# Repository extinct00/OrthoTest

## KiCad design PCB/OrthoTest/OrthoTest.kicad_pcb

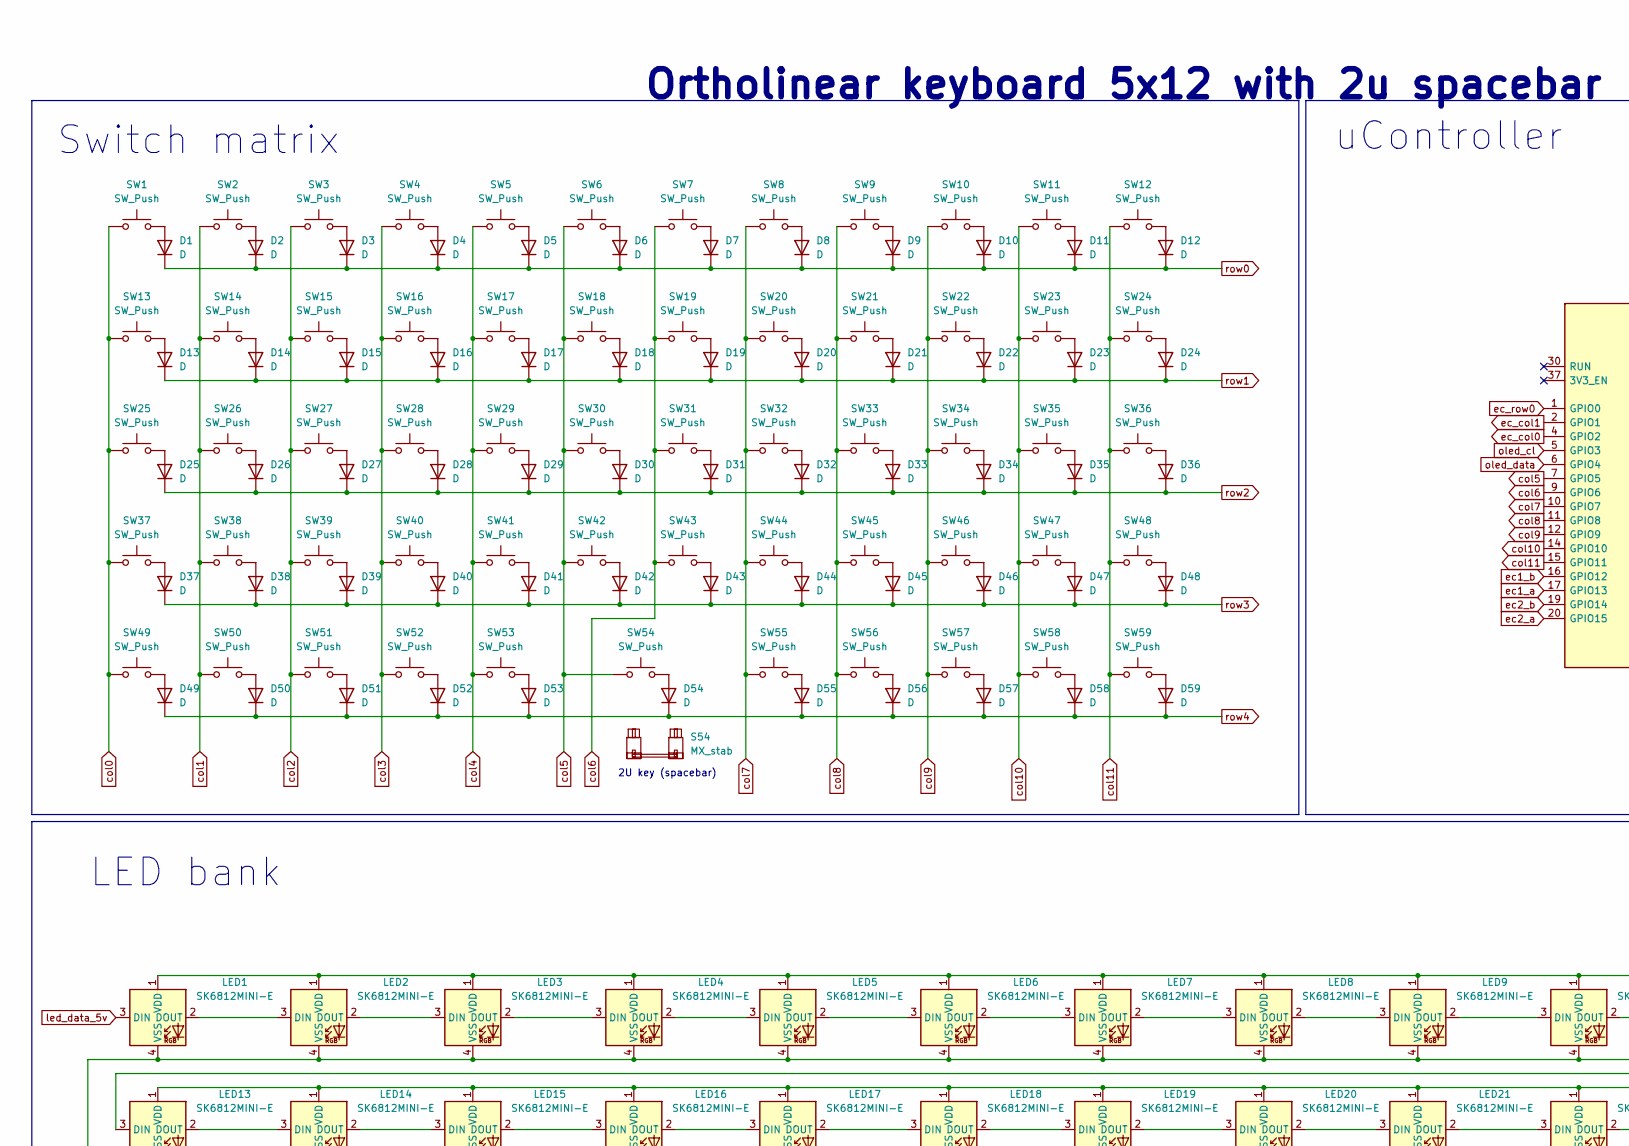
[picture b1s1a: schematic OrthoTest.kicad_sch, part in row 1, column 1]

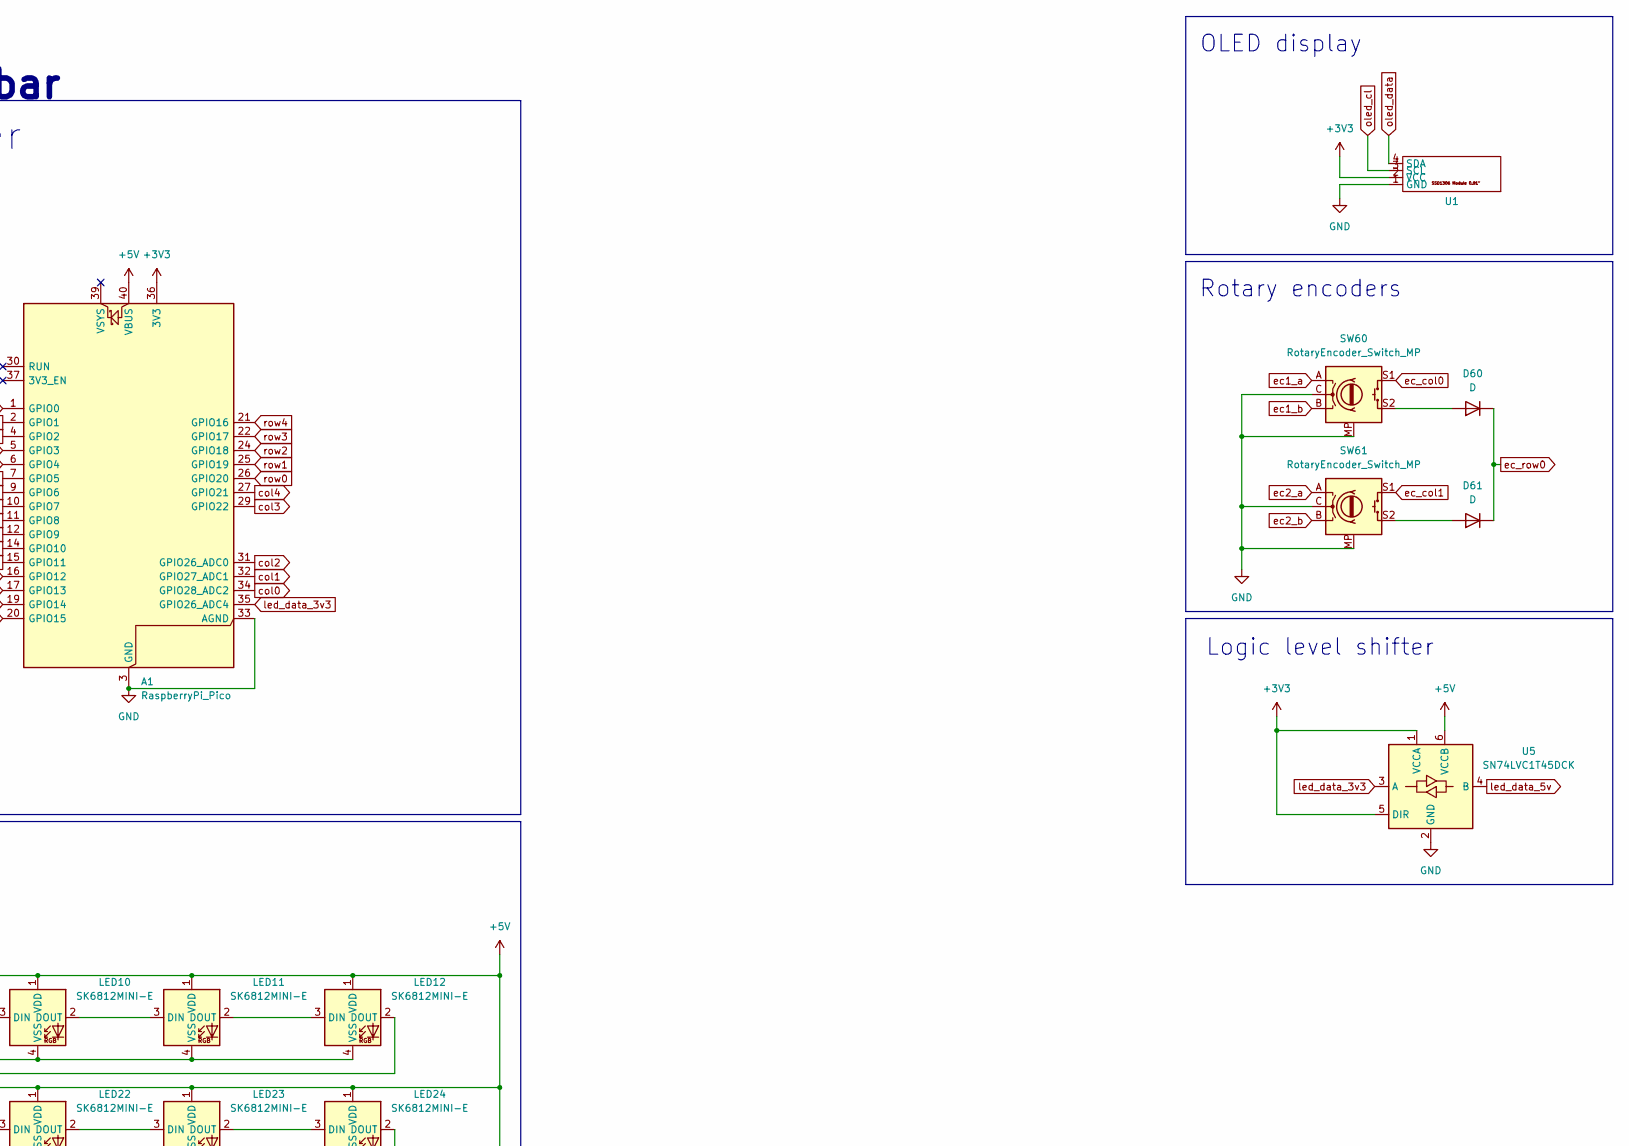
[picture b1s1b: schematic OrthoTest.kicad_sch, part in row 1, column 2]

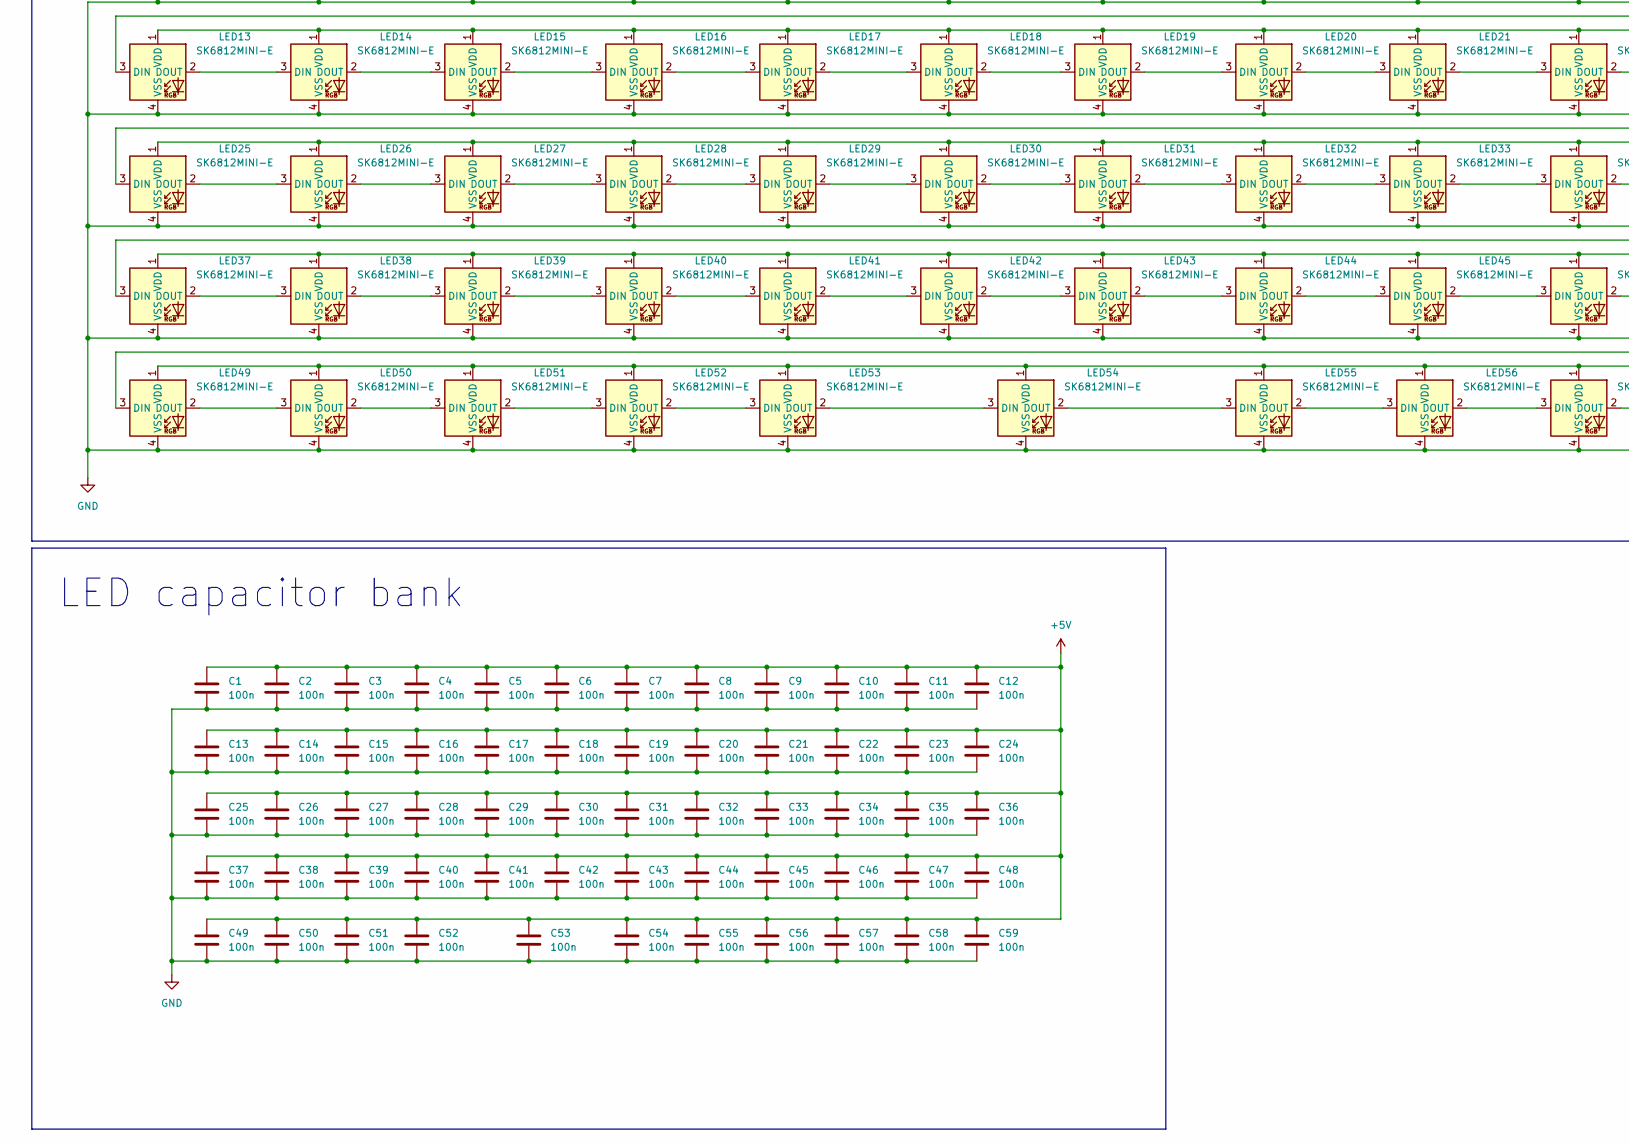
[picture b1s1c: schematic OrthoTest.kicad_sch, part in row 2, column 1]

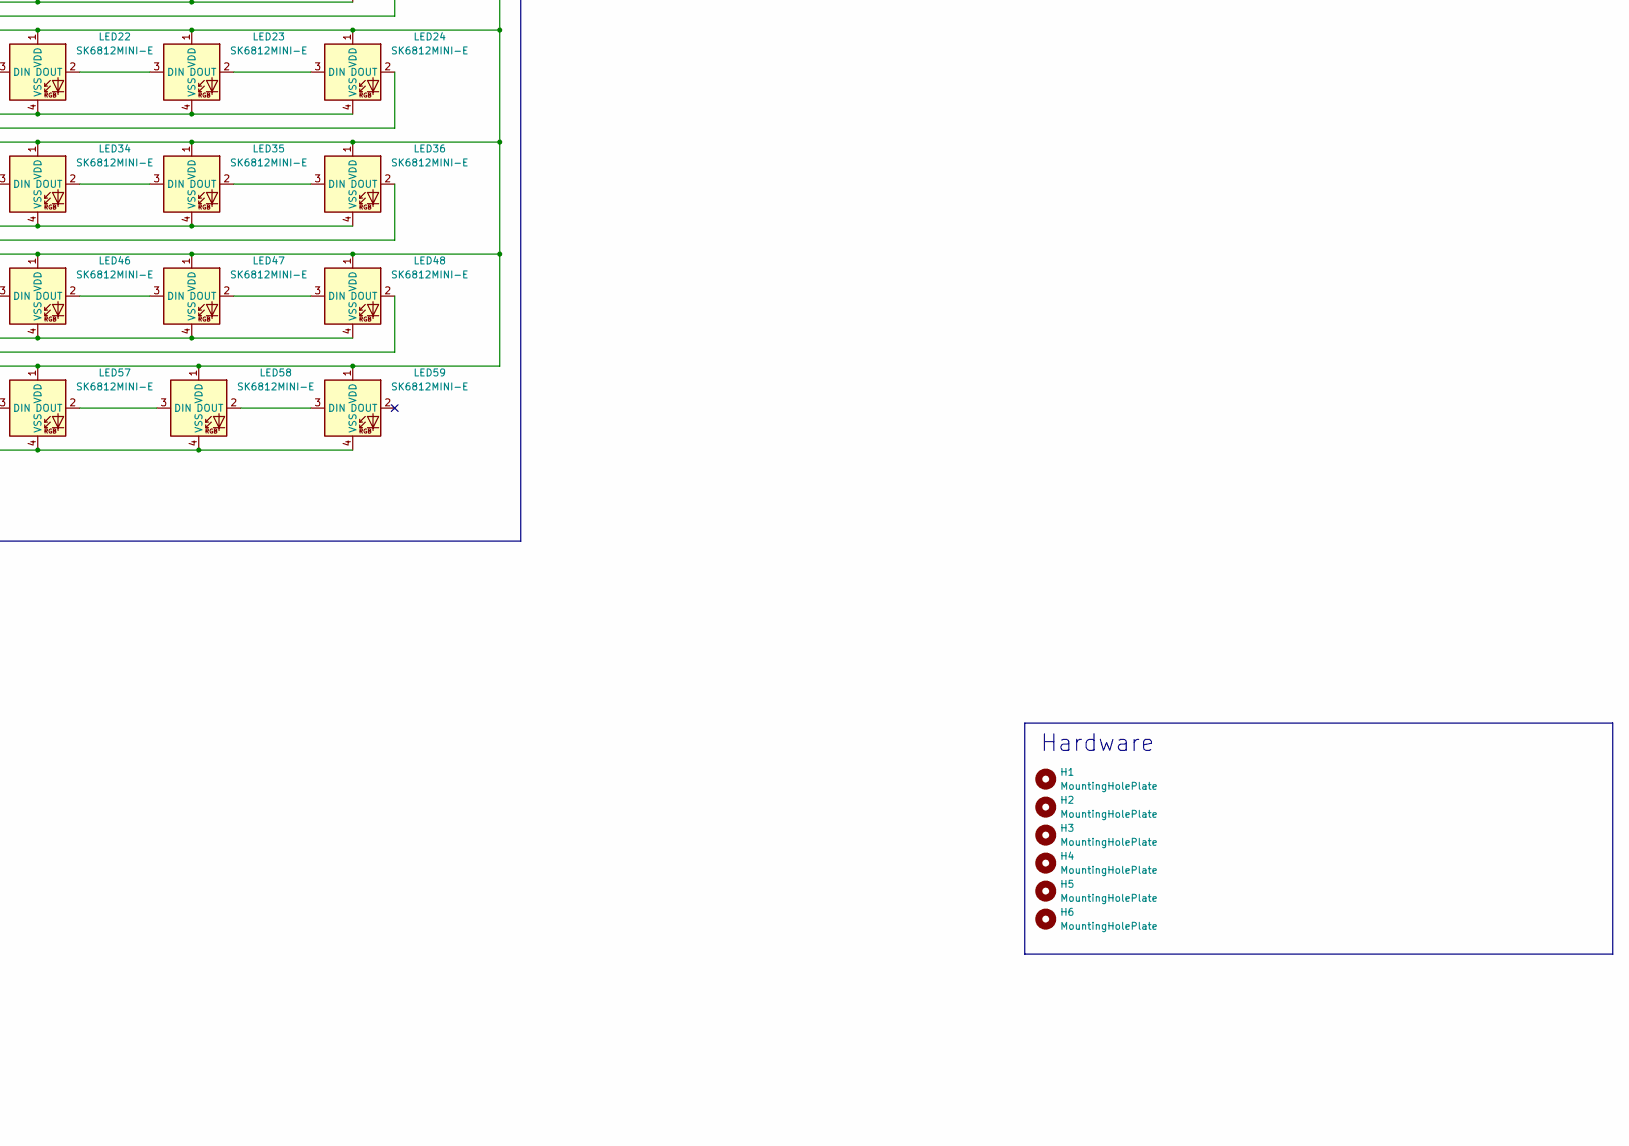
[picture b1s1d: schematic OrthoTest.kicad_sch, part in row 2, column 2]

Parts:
A1: RaspberryPi_Pico; RaspberryPi_Pico_Common_THT
C1, C2, C3, C4, C5, C6, C7, C8, C9, C10, C11, C12, C13, C14, C15, C16, C17, C18, C19, C20, C21, C22, C23, C24, C25, C26, C27, C28, C29, C30, C31, C32, C33, C34, C35, C36, C37, C38, C39, C40, C41, C42, C43, C44, C45, C46, C47, C48, C49, C50, C51, C52, C53, C54, C55, C56, C57, C58, C59: 100n; C_0603_1608Metric
D1, D2, D3, D4, D5, D6, D7, D8, D9, D10, D11, D12, D13, D14, D15, D16, D17, D18, D19, D20, D21, D22, D23, D24, D25, D26, D27, D28, D29, D30, D31, D32, D33, D34, D35, D36, D37, D38, D39, D40, D41, D42, D43, D44, D45, D46, D47, D48, D49, D50, D51, D52, D53, D54, D55, D56, D57, D58, D59, D60, D61: D; D_SOD-123_SmallArrow
H1, H2, H3, H4, H5, H6: MountingHolePlate; Spacer_3.2mm
LED1, LED2, LED3, LED4, LED5, LED6, LED7, LED8, LED9, LED10, LED11, LED12, LED13, LED14, LED15, LED16, LED17, LED18, LED19, LED20, LED21, LED22, LED23, LED24, LED25, LED26, LED27, LED28, LED29, LED30, LED31, LED32, LED33, LED34, LED35, LED36, LED37, LED38, LED39, LED40, LED41, LED42, LED43, LED44, LED45, LED46, LED47, LED48, LED49, LED50, LED51, LED52, LED53, LED54, LED55, LED56, LED57, LED58, LED59: SK6812MINI-E; LED_6028R
S54: MX_stab; STAB_MX_2u
SW1, SW2, SW3, SW4, SW5, SW6, SW7, SW8, SW9, SW10, SW11, SW12, SW13, SW14, SW15, SW16, SW17, SW18, SW19, SW20, SW21, SW22, SW23, SW24, SW25, SW26, SW27, SW28, SW29, SW30, SW31, SW32, SW33, SW34, SW35, SW36, SW37, SW38, SW39, SW40, SW41, SW42, SW43, SW44, SW45, SW46, SW47, SW48, SW49, SW50, SW51, SW52, SW53, SW54, SW55, SW56, SW57, SW58, SW59: SW_Push; SW_Redragon_LowProfile_PCB_1.00u
SW60, SW61: RotaryEncoder_Switch_MP; RotaryEncoder_Alps_EC11E-Switch_Vertical_H20mm
U1: SSD1306-0.91-OLED-4pin-128x32
U5: SN74LVC1T45DCK; SOT-363_SC-70-6

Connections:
+3V3: A1.36 (3V3), U1.2 (VCC), U5.1 (VCCA), U5.5 (DIR)
+5V: A1.40 (VBUS), C1.1, C2.1, C3.1, C4.1, C5.1, C6.1, C7.1, C8.1, C9.1, C10.1, C11.1, C12.1, C13.1, C14.1, C15.1, C16.1, C17.1, C18.1, C19.1, C20.1, C21.1, C22.1, C23.1, C24.1, C25.1, C26.1, C27.1, C28.1, C29.1, C30.1, C31.1, C32.1, C33.1, C34.1, C35.1, C36.1, C37.1, C38.1, C39.1, C40.1, C41.1, C42.1, C43.1, C44.1, C45.1, C46.1, C47.1, C48.1, C49.1, C50.1, C51.1, C52.1, C53.1, C54.1, C55.1, C56.1, C57.1, C58.1, C59.1, LED1.1 (VDD), LED2.1 (VDD), LED3.1 (VDD), LED4.1 (VDD), LED5.1 (VDD), LED6.1 (VDD), LED7.1 (VDD), LED8.1 (VDD), LED9.1 (VDD), LED10.1 (VDD), LED11.1 (VDD), LED12.1 (VDD), LED13.1 (VDD), LED14.1 (VDD), LED15.1 (VDD), LED16.1 (VDD), LED17.1 (VDD), LED18.1 (VDD), LED19.1 (VDD), LED20.1 (VDD), LED21.1 (VDD), LED22.1 (VDD), LED23.1 (VDD), LED24.1 (VDD), LED25.1 (VDD), LED26.1 (VDD), LED27.1 (VDD), LED28.1 (VDD), LED29.1 (VDD), LED30.1 (VDD), LED31.1 (VDD), LED32.1 (VDD), LED33.1 (VDD), LED34.1 (VDD), LED35.1 (VDD), LED36.1 (VDD), LED37.1 (VDD), LED38.1 (VDD), LED39.1 (VDD), LED40.1 (VDD), LED41.1 (VDD), LED42.1 (VDD), LED43.1 (VDD), LED44.1 (VDD), LED45.1 (VDD), LED46.1 (VDD), LED47.1 (VDD), LED48.1 (VDD), LED49.1 (VDD), LED50.1 (VDD), LED51.1 (VDD), LED52.1 (VDD), LED53.1 (VDD), LED54.1 (VDD), LED55.1 (VDD), LED56.1 (VDD), LED57.1 (VDD), LED58.1 (VDD), LED59.1 (VDD), U5.6 (VCCB)
GND: A1.3 (GND), A1.8 (GND), A1.13 (GND), A1.18 (GND), A1.23 (GND), A1.28 (GND), A1.33 (AGND), A1.38 (GND), C1.2, C2.2, C3.2, C4.2, C5.2, C6.2, C7.2, C8.2, C9.2, C10.2, C11.2, C12.2, C13.2, C14.2, C15.2, C16.2, C17.2, C18.2, C19.2, C20.2, C21.2, C22.2, C23.2, C24.2, C25.2, C26.2, C27.2, C28.2, C29.2, C30.2, C31.2, C32.2, C33.2, C34.2, C35.2, C36.2, C37.2, C38.2, C39.2, C40.2, C41.2, C42.2, C43.2, C44.2, C45.2, C46.2, C47.2, C48.2, C49.2, C50.2, C51.2, C52.2, C53.2, C54.2, C55.2, C56.2, C57.2, C58.2, C59.2, LED1.4 (VSS), LED2.4 (VSS), LED3.4 (VSS), LED4.4 (VSS), LED5.4 (VSS), LED6.4 (VSS), LED7.4 (VSS), LED8.4 (VSS), LED9.4 (VSS), LED10.4 (VSS), LED11.4 (VSS), LED12.4 (VSS), LED13.4 (VSS), LED14.4 (VSS), LED15.4 (VSS), LED16.4 (VSS), LED17.4 (VSS), LED18.4 (VSS), LED19.4 (VSS), LED20.4 (VSS), LED21.4 (VSS), LED22.4 (VSS), LED23.4 (VSS), LED24.4 (VSS), LED25.4 (VSS), LED26.4 (VSS), LED27.4 (VSS), LED28.4 (VSS), LED29.4 (VSS), LED30.4 (VSS), LED31.4 (VSS), LED32.4 (VSS), LED33.4 (VSS), LED34.4 (VSS), LED35.4 (VSS), LED36.4 (VSS), LED37.4 (VSS), LED38.4 (VSS), LED39.4 (VSS), LED40.4 (VSS), LED41.4 (VSS), LED42.4 (VSS), LED43.4 (VSS), LED44.4 (VSS), LED45.4 (VSS), LED46.4 (VSS), LED47.4 (VSS), LED48.4 (VSS), LED49.4 (VSS), LED50.4 (VSS), LED51.4 (VSS), LED52.4 (VSS), LED53.4 (VSS), LED54.4 (VSS), LED55.4 (VSS), LED56.4 (VSS), LED57.4 (VSS), LED58.4 (VSS), LED59.4 (VSS), SW60.C, SW60.MP, SW61.C, SW61.MP, U1.1 (GND), U5.2 (GND)
unnamed: D1.2 (A), SW1.2
unnamed: D2.2 (A), SW2.2
unnamed: D3.2 (A), SW3.2
unnamed: D4.2 (A), SW4.2
unnamed: D5.2 (A), SW5.2
unnamed: D6.2 (A), SW6.2
unnamed: D7.2 (A), SW7.2
unnamed: D8.2 (A), SW8.2
unnamed: D9.2 (A), SW9.2
unnamed: D10.2 (A), SW10.2
unnamed: D11.2 (A), SW11.2
unnamed: D12.2 (A), SW12.2
unnamed: D13.2 (A), SW13.2
unnamed: D14.2 (A), SW14.2
unnamed: D15.2 (A), SW15.2
unnamed: D16.2 (A), SW16.2
unnamed: D17.2 (A), SW17.2
unnamed: D18.2 (A), SW18.2
unnamed: D19.2 (A), SW19.2
unnamed: D20.2 (A), SW20.2
unnamed: D21.2 (A), SW21.2
unnamed: D22.2 (A), SW22.2
unnamed: D23.2 (A), SW23.2
unnamed: D24.2 (A), SW24.2
unnamed: D25.2 (A), SW25.2
unnamed: D26.2 (A), SW26.2
unnamed: D27.2 (A), SW27.2
unnamed: D28.2 (A), SW28.2
unnamed: D29.2 (A), SW29.2
unnamed: D30.2 (A), SW30.2
unnamed: D31.2 (A), SW31.2
unnamed: D32.2 (A), SW32.2
unnamed: D33.2 (A), SW33.2
unnamed: D34.2 (A), SW34.2
unnamed: D35.2 (A), SW35.2
unnamed: D36.2 (A), SW36.2
unnamed: D37.2 (A), SW37.2
unnamed: D38.2 (A), SW38.2
unnamed: D39.2 (A), SW39.2
unnamed: D40.2 (A), SW40.2
unnamed: D41.2 (A), SW41.2
unnamed: D42.2 (A), SW42.2
unnamed: D43.2 (A), SW43.2
unnamed: D44.2 (A), SW44.2
unnamed: D45.2 (A), SW45.2
unnamed: D46.2 (A), SW46.2
unnamed: D47.2 (A), SW47.2
unnamed: D48.2 (A), SW48.2
unnamed: D49.2 (A), SW49.2
unnamed: D50.2 (A), SW50.2
unnamed: D51.2 (A), SW51.2
unnamed: D52.2 (A), SW52.2
unnamed: D53.2 (A), SW53.2
unnamed: D54.2 (A), SW54.2
unnamed: D55.2 (A), SW55.2
unnamed: D56.2 (A), SW56.2
unnamed: D57.2 (A), SW57.2
unnamed: D58.2 (A), SW58.2
unnamed: D59.2 (A), SW59.2
unnamed: D60.2 (A), SW60.S2
unnamed: D61.2 (A), SW61.S2
unnamed: LED1.2 (DOUT), LED2.3 (DIN)
unnamed: LED2.2 (DOUT), LED3.3 (DIN)
unnamed: LED3.2 (DOUT), LED4.3 (DIN)
unnamed: LED4.2 (DOUT), LED5.3 (DIN)
unnamed: LED5.2 (DOUT), LED6.3 (DIN)
unnamed: LED6.2 (DOUT), LED7.3 (DIN)
unnamed: LED7.2 (DOUT), LED8.3 (DIN)
unnamed: LED8.2 (DOUT), LED9.3 (DIN)
unnamed: LED9.2 (DOUT), LED10.3 (DIN)
unnamed: LED10.2 (DOUT), LED11.3 (DIN)
unnamed: LED11.2 (DOUT), LED12.3 (DIN)
unnamed: LED12.2 (DOUT), LED13.3 (DIN)
unnamed: LED13.2 (DOUT), LED14.3 (DIN)
unnamed: LED14.2 (DOUT), LED15.3 (DIN)
unnamed: LED15.2 (DOUT), LED16.3 (DIN)
unnamed: LED16.2 (DOUT), LED17.3 (DIN)
unnamed: LED17.2 (DOUT), LED18.3 (DIN)
unnamed: LED18.2 (DOUT), LED19.3 (DIN)
unnamed: LED19.2 (DOUT), LED20.3 (DIN)
unnamed: LED20.2 (DOUT), LED21.3 (DIN)
unnamed: LED21.2 (DOUT), LED22.3 (DIN)
unnamed: LED22.2 (DOUT), LED23.3 (DIN)
unnamed: LED23.2 (DOUT), LED24.3 (DIN)
unnamed: LED24.2 (DOUT), LED25.3 (DIN)
unnamed: LED25.2 (DOUT), LED26.3 (DIN)
unnamed: LED26.2 (DOUT), LED27.3 (DIN)
unnamed: LED27.2 (DOUT), LED28.3 (DIN)
unnamed: LED28.2 (DOUT), LED29.3 (DIN)
unnamed: LED29.2 (DOUT), LED30.3 (DIN)
unnamed: LED30.2 (DOUT), LED31.3 (DIN)
unnamed: LED31.2 (DOUT), LED32.3 (DIN)
unnamed: LED32.2 (DOUT), LED33.3 (DIN)
unnamed: LED33.2 (DOUT), LED34.3 (DIN)
unnamed: LED34.2 (DOUT), LED35.3 (DIN)
unnamed: LED35.2 (DOUT), LED36.3 (DIN)
unnamed: LED36.2 (DOUT), LED37.3 (DIN)
unnamed: LED37.2 (DOUT), LED38.3 (DIN)
unnamed: LED38.2 (DOUT), LED39.3 (DIN)
unnamed: LED39.2 (DOUT), LED40.3 (DIN)
unnamed: LED40.2 (DOUT), LED41.3 (DIN)
unnamed: LED41.2 (DOUT), LED42.3 (DIN)
unnamed: LED42.2 (DOUT), LED43.3 (DIN)
unnamed: LED43.2 (DOUT), LED44.3 (DIN)
unnamed: LED44.2 (DOUT), LED45.3 (DIN)
unnamed: LED45.2 (DOUT), LED46.3 (DIN)
unnamed: LED46.2 (DOUT), LED47.3 (DIN)
unnamed: LED47.2 (DOUT), LED48.3 (DIN)
unnamed: LED48.2 (DOUT), LED49.3 (DIN)
unnamed: LED49.2 (DOUT), LED50.3 (DIN)
unnamed: LED50.2 (DOUT), LED51.3 (DIN)
unnamed: LED51.2 (DOUT), LED52.3 (DIN)
unnamed: LED52.2 (DOUT), LED53.3 (DIN)
unnamed: LED53.2 (DOUT), LED54.3 (DIN)
unnamed: LED54.2 (DOUT), LED55.3 (DIN)
unnamed: LED55.2 (DOUT), LED56.3 (DIN)
unnamed: LED56.2 (DOUT), LED57.3 (DIN)
unnamed: LED57.2 (DOUT), LED58.3 (DIN)
unnamed: LED58.2 (DOUT), LED59.3 (DIN)
col0: A1.34 (GPIO28_ADC2), SW1.1, SW13.1, SW25.1, SW37.1, SW49.1
col1: A1.32 (GPIO27_ADC1), SW2.1, SW14.1, SW26.1, SW38.1, SW50.1
col2: A1.31 (GPIO26_ADC0), SW3.1, SW15.1, SW27.1, SW39.1, SW51.1
col3: A1.29 (GPIO22), SW4.1, SW16.1, SW28.1, SW40.1, SW52.1
col4: A1.27 (GPIO21), SW5.1, SW17.1, SW29.1, SW41.1, SW53.1
col5: A1.7 (GPIO5), SW6.1, SW18.1, SW30.1, SW42.1, SW54.1
col6: A1.9 (GPIO6), SW7.1, SW19.1, SW31.1, SW43.1
col7: A1.10 (GPIO7), SW8.1, SW20.1, SW32.1, SW44.1, SW55.1
col8: A1.11 (GPIO8), SW9.1, SW21.1, SW33.1, SW45.1, SW56.1
col9: A1.12 (GPIO9), SW10.1, SW22.1, SW34.1, SW46.1, SW57.1
col10: A1.14 (GPIO10), SW11.1, SW23.1, SW35.1, SW47.1, SW58.1
col11: A1.15 (GPIO11), SW12.1, SW24.1, SW36.1, SW48.1, SW59.1
ec1_a: A1.17 (GPIO13), SW60.A
ec1_b: A1.16 (GPIO12), SW60.B
ec2_a: A1.20 (GPIO15), SW61.A
ec2_b: A1.19 (GPIO14), SW61.B
ec_col0: A1.4 (GPIO2), SW60.S1
ec_col1: A1.2 (GPIO1), SW61.S1
ec_row0: A1.1 (GPIO0), D60.1 (K), D61.1 (K)
led_data_3v3: A1.35 (GPIO26_ADC4), U5.3 (A)
led_data_5v: LED1.3 (DIN), U5.4 (B)
oled_cl: A1.5 (GPIO3), U1.3 (SCL)
oled_data: A1.6 (GPIO4), U1.4 (SDA)
row0: A1.26 (GPIO20), D1.1 (K), D2.1 (K), D3.1 (K), D4.1 (K), D5.1 (K), D6.1 (K), D7.1 (K), D8.1 (K), D9.1 (K), D10.1 (K), D11.1 (K), D12.1 (K)
row1: A1.25 (GPIO19), D13.1 (K), D14.1 (K), D15.1 (K), D16.1 (K), D17.1 (K), D18.1 (K), D19.1 (K), D20.1 (K), D21.1 (K), D22.1 (K), D23.1 (K), D24.1 (K)
row2: A1.24 (GPIO18), D25.1 (K), D26.1 (K), D27.1 (K), D28.1 (K), D29.1 (K), D30.1 (K), D31.1 (K), D32.1 (K), D33.1 (K), D34.1 (K), D35.1 (K), D36.1 (K)
row3: A1.22 (GPIO17), D37.1 (K), D38.1 (K), D39.1 (K), D40.1 (K), D41.1 (K), D42.1 (K), D43.1 (K), D44.1 (K), D45.1 (K), D46.1 (K), D47.1 (K), D48.1 (K)
row4: A1.21 (GPIO16), D49.1 (K), D50.1 (K), D51.1 (K), D52.1 (K), D53.1 (K), D54.1 (K), D55.1 (K), D56.1 (K), D57.1 (K), D58.1 (K), D59.1 (K)

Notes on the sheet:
Switch matrix
OLED display
Hardware
Logic level shifter
Rotary encoders
LED bank
LED capacitor bank
2U key (spacebar)
uController
Ortholinear keyboard 5x12 with 2u spacebar

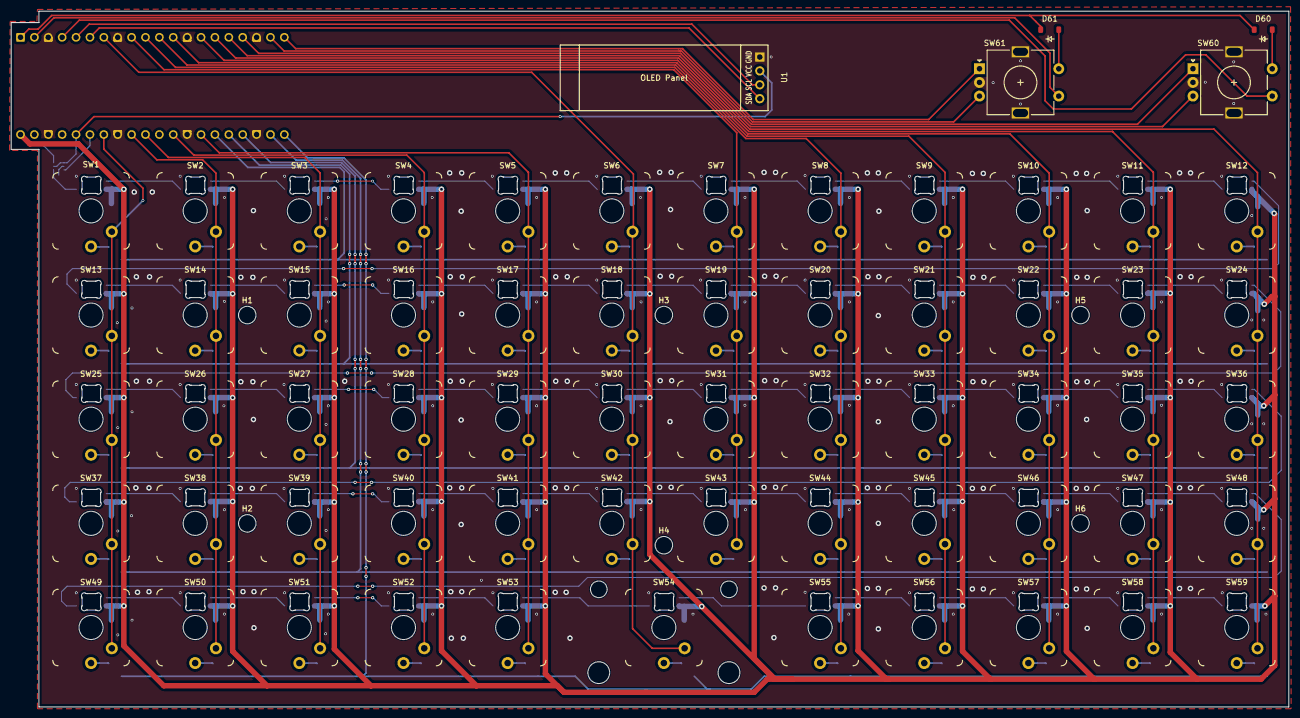
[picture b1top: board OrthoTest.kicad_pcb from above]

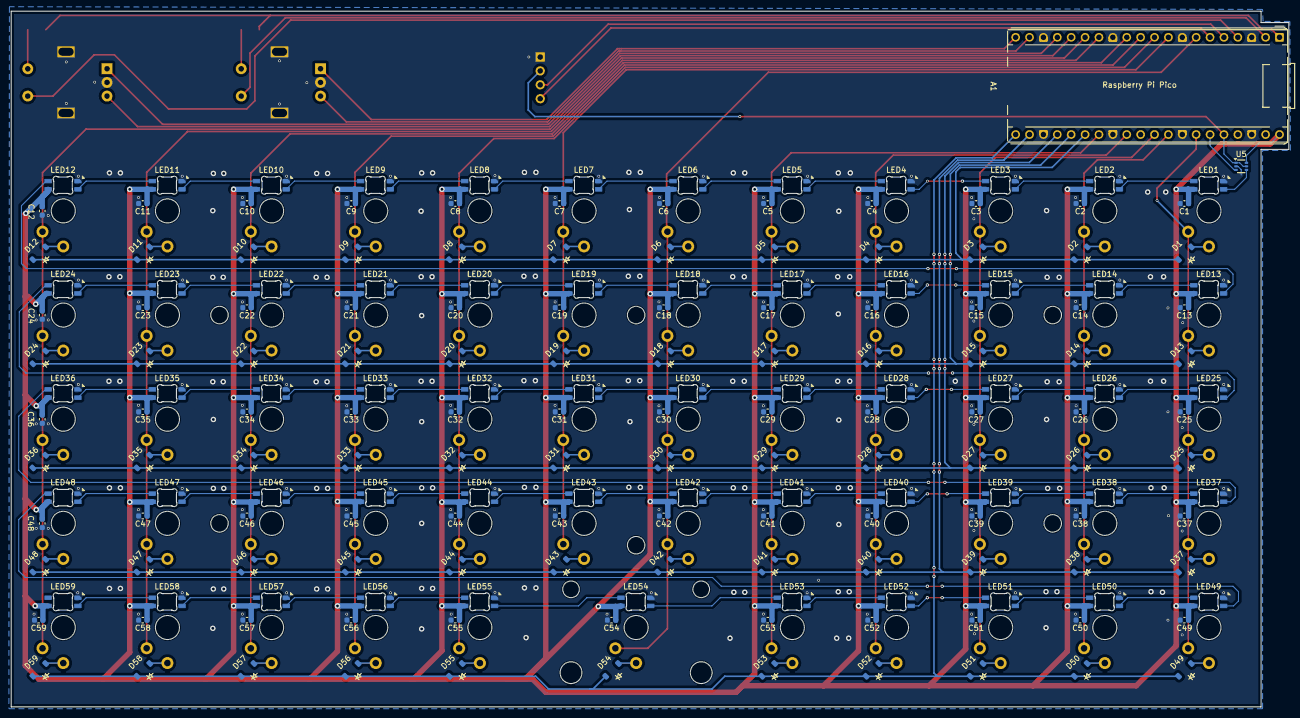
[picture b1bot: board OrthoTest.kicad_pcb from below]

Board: 2 copper layers, 233.7 x 127.2 mm, 250 parts (179 on the bottom side), 150 nets.

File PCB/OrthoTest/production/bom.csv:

Designator,Footprint,Quantity,Value,LCSC Part #
A1,RaspberryPi_Pico_Common_THT,1,RaspberryPi_Pico,
"C1, C10, C11, C12, C13, C14, C15, C16, C17, C18, C19, C2, C20, C21, C22, C23, C24, C25, C26, C27, C28, C29, C3, C30, C31, C32, C33, C34, C35, C36, C37, C38, C39, C4, C40, C41, C42, C43, C44, C45, C46, C47, C48, C49, C5, C50, C51, C52, C53, C54, C55, C56, C57, C58, C59, C6, C7, C8, C9",0603,59,100n,
"D1, D10, D11, D12, D13, D14, D15, D16, D17, D18, D19, D2, D20, D21, D22, D23, D24, D25, D26, D27, D28, D29, D3, D30, D31, D32, D33, D34, D35, D36, D37, D38, D39, D4, D40, D41, D42, D43, D44, D45, D46, D47, D48, D49, D5, D50, D51, D52, D53, D54, D55, D56, D57, D58, D59, D6, D60, D61, D7, D8, D9",D_SOD-123_SmallArrow,61,D,
"LED1, LED10, LED11, LED12, LED13, LED14, LED15, LED16, LED17, LED18, LED19, LED2, LED20, LED21, LED22, LED23, LED24, LED25, LED26, LED27, LED28, LED29, LED3, LED30, LED31, LED32, LED33, LED34, LED35, LED36, LED37, LED38, LED39, LED4, LED40, LED41, LED42, LED43, LED44, LED45, LED46, LED47, LED48, LED49, LED5, LED50, LED51, LED52, LED53, LED54, LED55, LED56, LED57, LED58, LED59, LED6, LED7, LED8, LED9",LED_6028R,59,SK6812MINI-E,
S54,STAB_MX_2u,1,MX_stab,
"SW1, SW10, SW11, SW12, SW13, SW14, SW15, SW16, SW17, SW18, SW19, SW2, SW20, SW21, SW22, SW23, SW24, SW25, SW26, SW27, SW28, SW29, SW3, SW30, SW31, SW32, SW33, SW34, SW35, SW36, SW37, SW38, SW39, SW4, SW40, SW41, SW42, SW43, SW44, SW45, SW46, SW47, SW48, SW49, SW5, SW50, SW51, SW52, SW53, SW54, SW55, SW56, SW57, SW58, SW59, SW6, SW7, SW8, SW9",SW_Redragon_LowProfile_PCB_1.00u,59,SW_Push,
"SW60, SW61",RotaryEncoder_Alps_EC11E-Switch_Vertical_H20mm,2,RotaryEncoder_Switch_MP,
U1,SSD1306-0.91-OLED-4pin-128x32,1,~,
U5,SOT-363_SC-70-6,1,SN74LVC1T45DCK,

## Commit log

2025-07-13 started working on it
2025-07-13 started working on v1
2025-07-13 added some documentation
2025-07-14 worked on it a lil
2025-07-14 worked a lil on it
2025-07-15 done little work, not enought energy today :(
2025-07-16 added libraries and placed pcb components
2025-07-17 finished routing pcb
2025-07-17 generated gerbers and prod files
2025-07-22 fixed ucontroller usb c position and added grounding vias
2025-07-22 spaced encoders additional 10mm aparart
2025-07-23 rerouting ucontroller
2025-07-23 added level shifter and finished rerouting
